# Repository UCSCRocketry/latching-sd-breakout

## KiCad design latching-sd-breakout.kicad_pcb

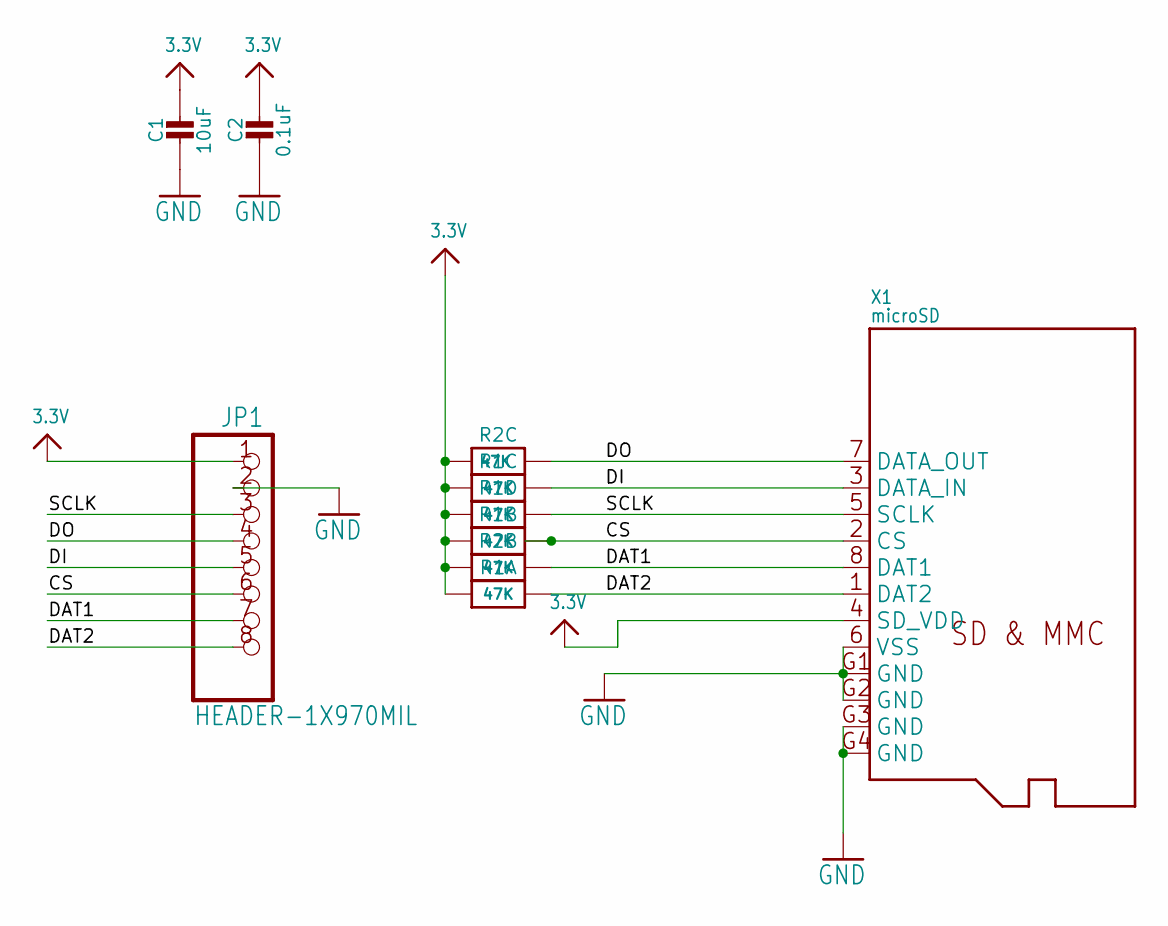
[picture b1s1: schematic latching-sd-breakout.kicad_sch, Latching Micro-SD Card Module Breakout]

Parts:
C1: 10uF; C_0805_2012Metric
C2: 0.1uF; C_0603_1608Metric
JP1: HEADER-1X970MIL; Micro_SD
R1, R2: 47K; R_Array_Concave_4x0603
X1: microSD; CONN_47219-2001_MOL

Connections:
3.3V: C1.1, C2.1, JP1.1, R1.1, R1.2 (1), R1.3 (1), R1.4 (1), R2.2 (1), R2.3 (1), X1.4 (SD_VDD)
/CS: JP1.6, R1.7 (2), X1.2 (CS)
/DAT1: JP1.7, R2.7 (2), X1.8 (DAT1)
/DAT2: JP1.8, R1.8 (2), X1.1 (DAT2)
/DI: JP1.5, R1.6 (2), X1.3 (DATA_IN)
/DO: JP1.4, R2.6 (2), X1.7 (DATA_OUT)
/SCLK: JP1.3, R1.5 (2), X1.5 (SCLK)
GND: C1.2, C2.2, JP1.2, X1.6 (VSS), X1.G1 (GND), X1.G2 (GND), X1.G3 (GND), X1.G4 (GND)

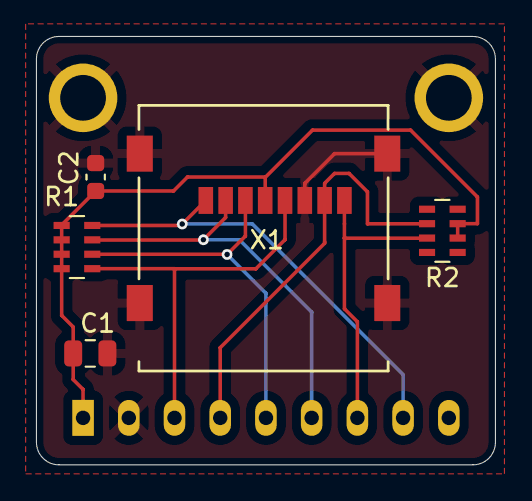
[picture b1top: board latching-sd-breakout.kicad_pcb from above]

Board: 2 copper layers, 25.5 x 23.8 mm, 6 parts (0 on the bottom side), 8 nets.

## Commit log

2026-01-26 add schematic, symbol, and pcb files
2026-01-29 pass drc
2026-01-29 fix routing angles
2026-02-02 changed resistor arrays
2026-02-02 fillet it
2026-03-06 replace 0502 resister arrays with 0603
